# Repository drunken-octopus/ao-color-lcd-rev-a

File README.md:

# ao-color-lcd-rev-a
Revision A of the AlephObjects Color LCD Board, as originally archived from AlephObject's git repos in 2019.

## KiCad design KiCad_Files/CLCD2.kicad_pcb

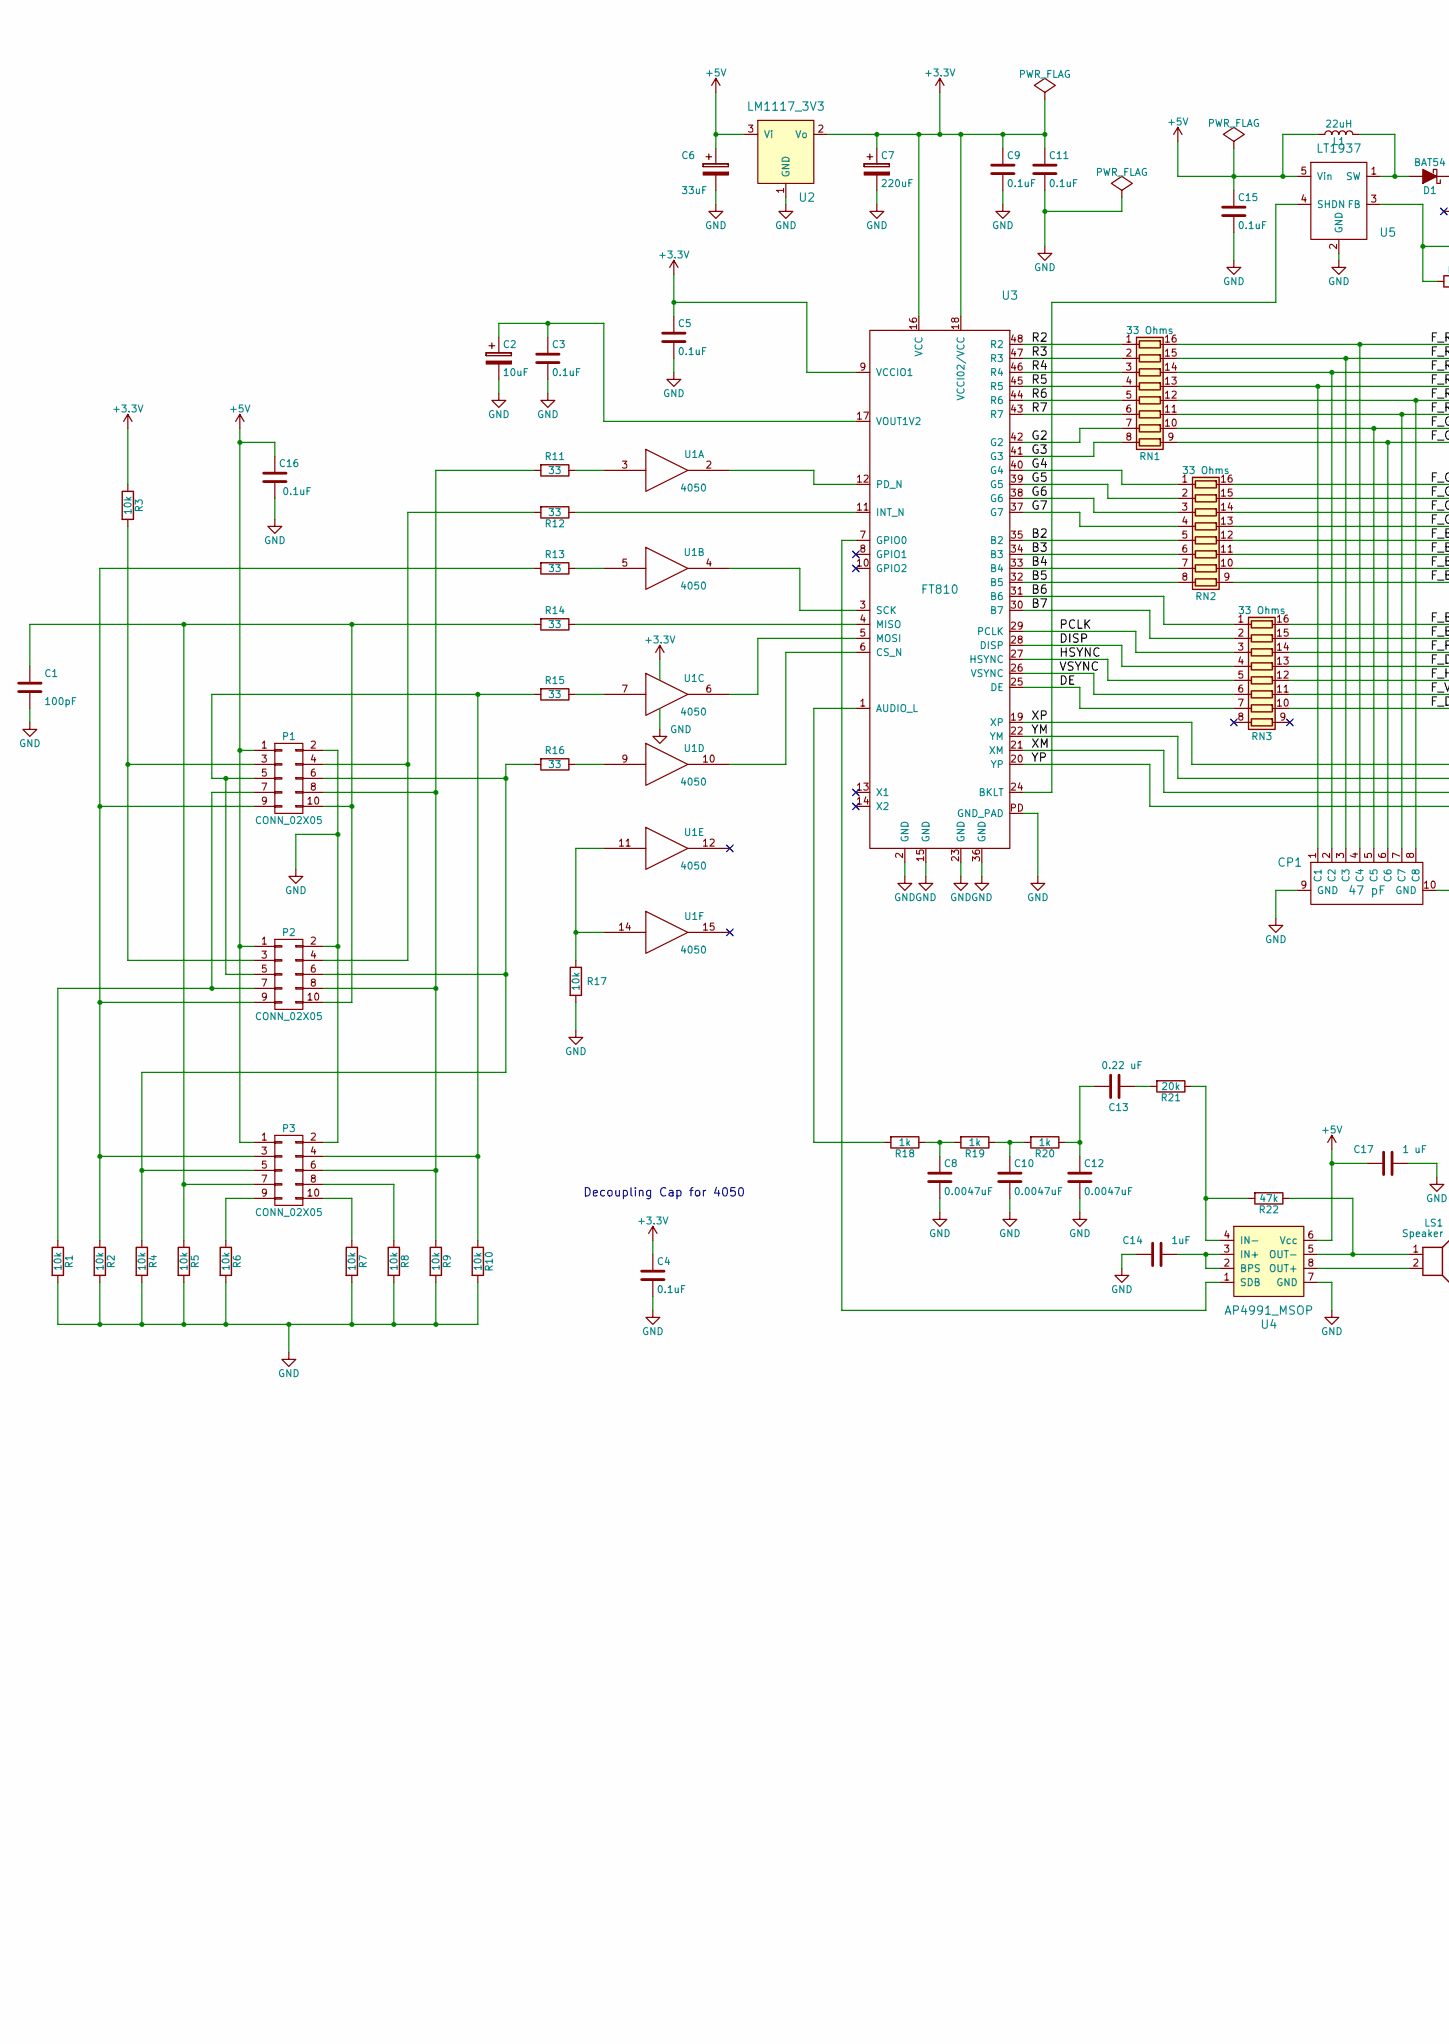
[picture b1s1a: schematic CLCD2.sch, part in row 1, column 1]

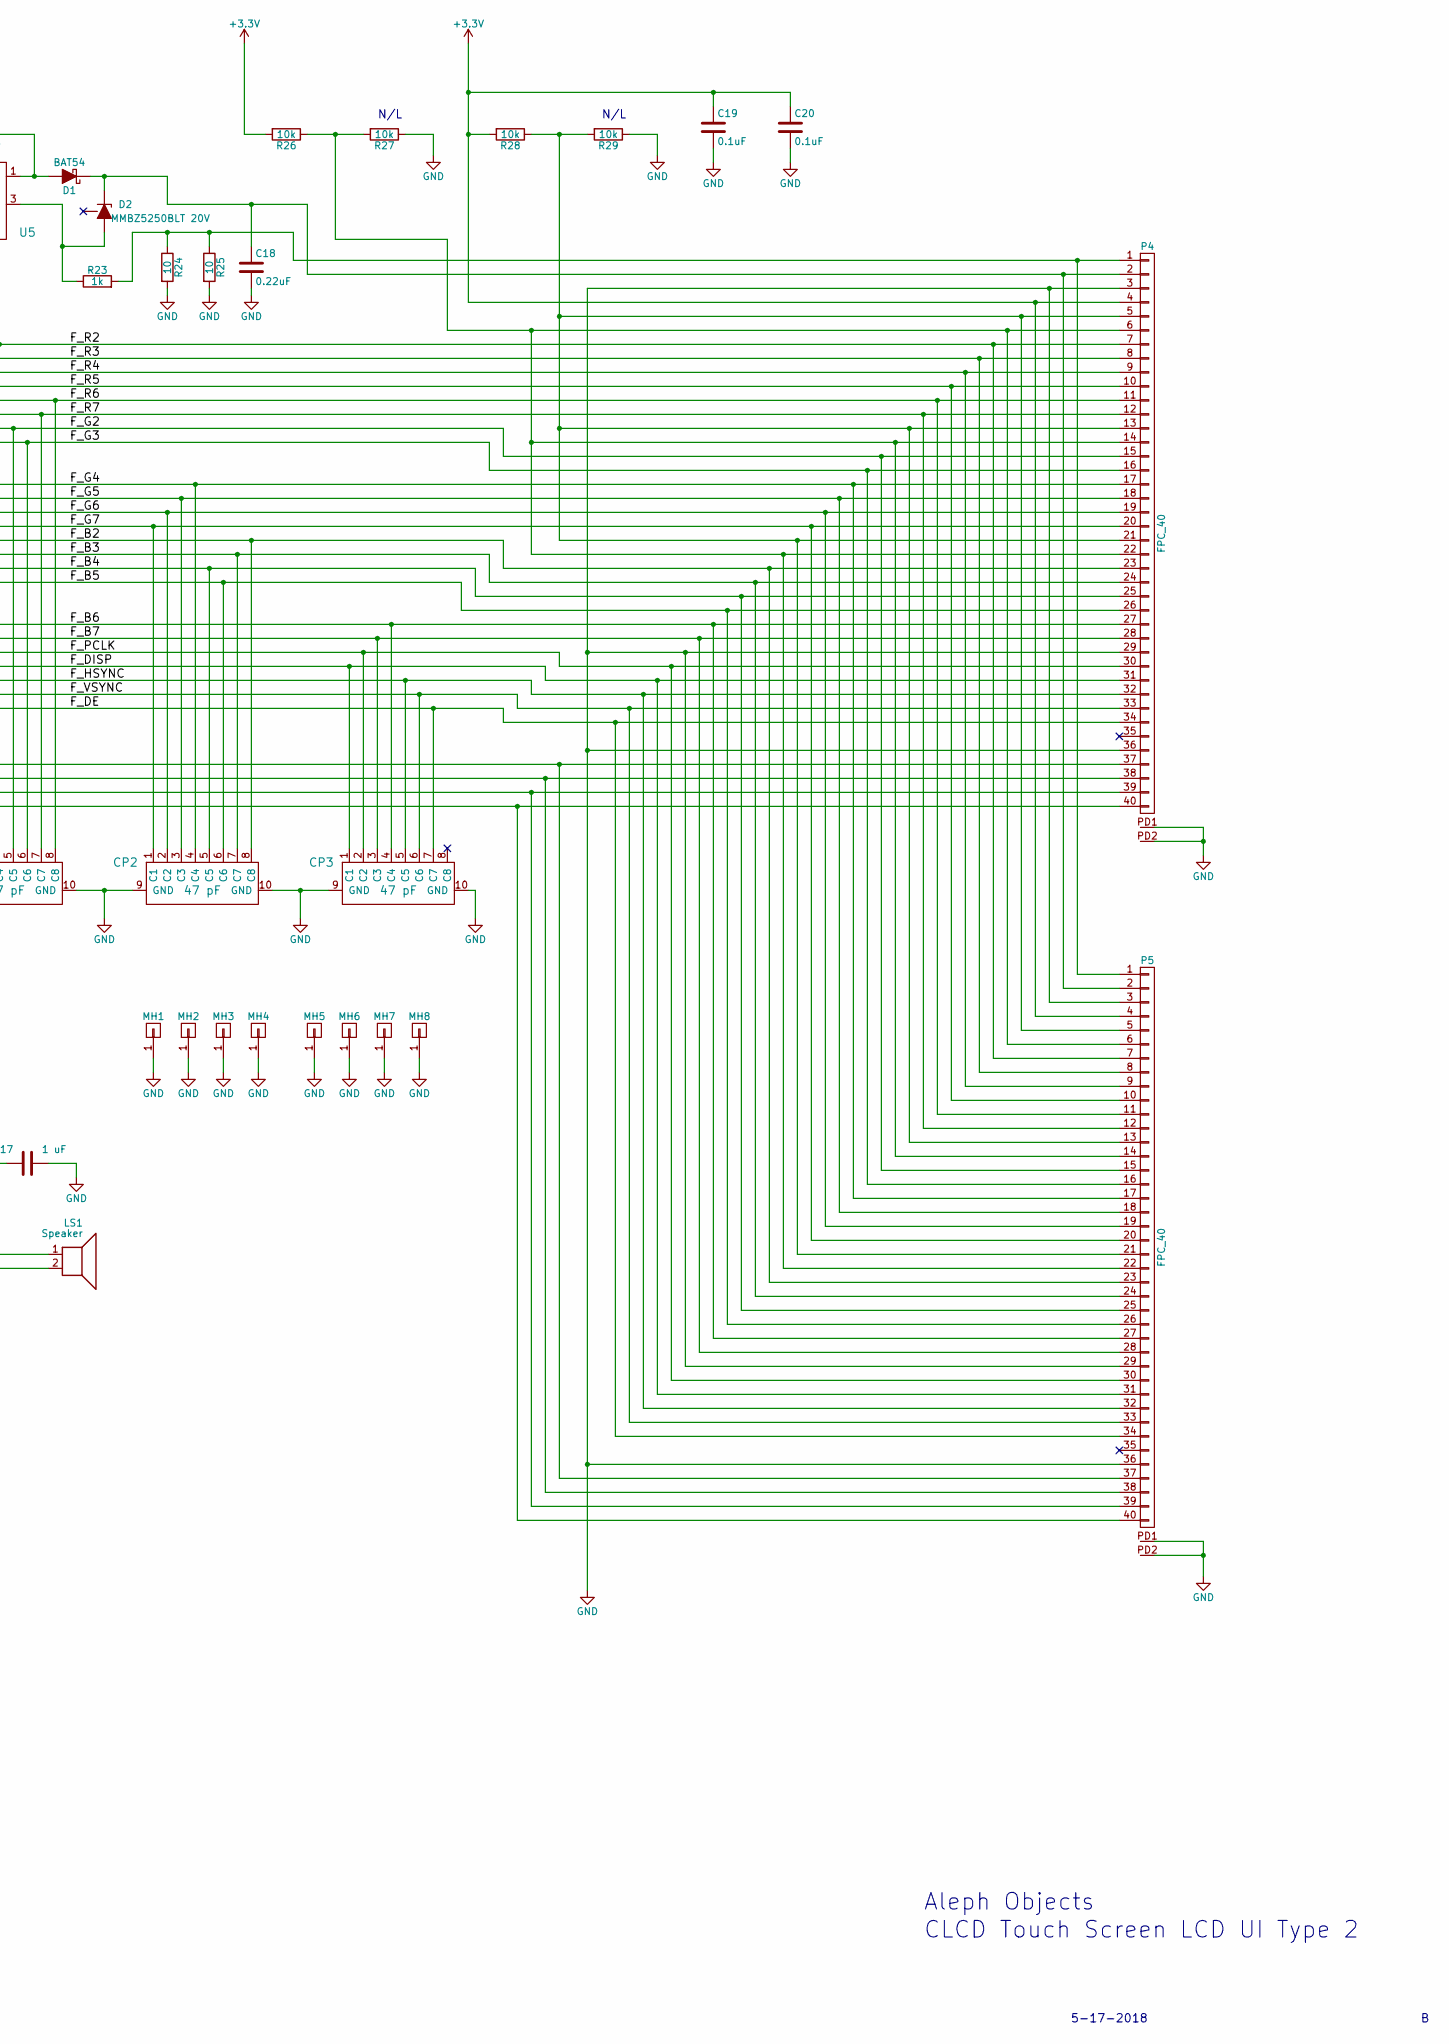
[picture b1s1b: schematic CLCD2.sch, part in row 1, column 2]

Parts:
C1: 100pF; C_0603_HandSoldering
C2: 10uF; TantalC_SizeD_EIA-7343_HandSoldering
C3, C4, C5, C9, C11, C15, C16, C19, C20: 0.1uF; C_0603_HandSoldering
C6: 33uF; TantalC_SizeD_EIA-7343_HandSoldering
C7: 220uF; TantalC_SizeD_EIA-7343_HandSoldering
C8, C10, C12: 0.0047uF; C_0603_HandSoldering
C13: 0.22 uF; C_0603_HandSoldering
C14: 1uF; C_0603_HandSoldering
C17: 1 uF; C_0603_HandSoldering
C18: 0.22uF; C_0603_HandSoldering
CP1, CP2, CP3: 47 pF; CPAK8
D1: BAT54; SOD-123
D2: MMBZ5250BLT 20V; SOT-23
L1: 22uH; Inductor_Taiyo-Yuden_MD-3030
LS1: Speaker; CVS_1508
MH1, MH2, MH3, MH4, MH5, MH6, MH7, MH8: CONN_01X01; MH_M3x6mm
P1, P2, P3: CONN_02X05; IDC_Header_Straight_10pins
P4, P5: FPC_40
R1, R2, R3, R4, R5, R6, R7, R8, R9, R10, R17, R26, R27, R28, R29: 10k; R_0603_HandSoldering
R11, R12, R13, R14, R15, R16: 33; R_0603_HandSoldering
R18, R19, R20, R23: 1k; R_0603_HandSoldering
R21: 20k; R_0603_HandSoldering
R22: 47k; R_0603_HandSoldering
R24, R25: 10; R_0603_HandSoldering
RN1, RN2, RN3: 33 Ohms; RPAK8
U1: 4050; SO-16-N
U2: LM1117_3V3; TO-252-2Lead
U3: FT810; VQFN_48_7x7
U4: AP4991_MSOP; MSOP8
U5: LT1937; SOT-23-5

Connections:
+3V3: C4.1, C5.1, C7.1, C9.1, C11.1, C19.1, C20.1, P4.4, P5.4, R3.1, R26.2, R28.2, U1.1 (VCC), U2.2 (Vo), U3.9 (VCCIO1), U3.16 (VCC), U3.18 (VCCI02/VCC)
+5V: C6.1, C15.1, C16.1, C17.2, L1.1, P1.1, P2.1, P3.1, U2.3 (Vi), U4.6 (Vcc), U5.5 (Vin)
/B2: RN2.5 (R5.1), U3.35 (B2)
/B3: RN2.6 (R6.1), U3.34 (B3)
/B4: RN2.7 (R7.1), U3.33 (B4)
/B5: RN2.8 (R8.1), U3.32 (B5)
/B6: RN3.1 (R1.1), U3.31 (B6)
/B7: RN3.2 (R2.1), U3.30 (B7)
/DE: RN3.7 (R7.1), U3.25 (DE)
/DISP: RN3.4 (R4.1), U3.28 (DISP)
/F_B2: CP2.8 (C8), P4.23, P5.23, RN2.12 (R5.2)
/F_B3: CP2.7 (C7), P4.24, P5.24, RN2.11 (R6.2)
/F_B4: CP2.5 (C5), P4.25, P5.25, RN2.10 (R7.2)
/F_B5: CP2.6 (C6), P4.26, P5.26, RN2.9 (R8.2)
/F_B6: CP3.4 (C4), P4.27, P5.27, RN3.16 (R1.2)
/F_B7: CP3.3 (C3), P4.28, P5.28, RN3.15 (R2.2)
/F_DE: CP3.7 (C7), P4.34, P5.34, RN3.10 (R7.2)
/F_DISP: CP3.1 (C1), P4.31, P5.31, RN3.13 (R4.2)
/F_G2: CP1.5 (C5), P4.15, P5.15, RN1.10 (R7.2)
/F_G3: CP1.6 (C6), P4.16, P5.16, RN1.9 (R8.2)
/F_G4: CP2.4 (C4), P4.17, P5.17, RN2.16 (R1.2)
/F_G5: CP2.3 (C3), P4.18, P5.18, RN2.15 (R2.2)
/F_G6: CP2.2 (C2), P4.19, P5.19, RN2.14 (R3.2)
/F_G7: CP2.1 (C1), P4.20, P5.20, RN2.13 (R4.2)
/F_HSYNC: CP3.5 (C5), P4.32, P5.32, RN3.12 (R5.2)
/F_PCLK: CP3.2 (C2), P4.30, P5.30, RN3.14 (R3.2)
/F_R2: CP1.4 (C4), P4.7, P5.7, RN1.16 (R1.2)
/F_R3: CP1.3 (C3), P4.8, P5.8, RN1.15 (R2.2)
/F_R4: CP1.2 (C2), P4.9, P5.9, RN1.14 (R3.2)
/F_R5: CP1.1 (C1), P4.10, P5.10, RN1.13 (R4.2)
/F_R6: CP1.8 (C8), P4.11, P5.11, RN1.12 (R5.2)
/F_R7: CP1.7 (C7), P4.12, P5.12, RN1.11 (R6.2)
/F_VSYNC: CP3.6 (C6), P4.33, P5.33, RN3.11 (R6.2)
/G2: RN1.7 (R7.1), U3.42 (G2)
/G3: RN1.8 (R8.1), U3.41 (G3)
/G4: RN2.1 (R1.1), U3.40 (G4)
/G5: RN2.2 (R2.1), U3.39 (G5)
/G6: RN2.3 (R3.1), U3.38 (G6)
/G7: RN2.4 (R4.1), U3.37 (G7)
/HSYNC: RN3.5 (R5.1), U3.27 (HSYNC)
/PCLK: RN3.3 (R3.1), U3.29 (PCLK)
/R2: RN1.1 (R1.1), U3.48 (R2)
/R3: RN1.2 (R2.1), U3.47 (R3)
/R4: RN1.3 (R3.1), U3.46 (R4)
/R5: RN1.4 (R4.1), U3.45 (R5)
/R6: RN1.5 (R5.1), U3.44 (R6)
/R7: RN1.6 (R6.1), U3.43 (R7)
/VSYNC: RN3.6 (R6.1), U3.26 (VSYNC)
/XM: P4.39, P5.39, U3.21 (XM)
/XP: P4.37, P5.37, U3.19 (XP)
/YM: P4.38, P5.38, U3.22 (YM)
/YP: P4.40, P5.40, U3.20 (YP)
GND: C1.2, C2.2, C3.2, C4.2, C5.2, C6.2, C7.2, C8.2, C9.2, C10.2, C11.2, C12.2, C14.2, C15.2, C16.2, C17.1, C18.2, C19.2, C20.2, CP1.9 (GND), CP1.10 (GND), CP2.9 (GND), CP2.10 (GND), CP3.9 (GND), CP3.10 (GND), MH1.1, MH2.1, MH3.1, MH4.1, MH5.1, MH6.1, MH7.1, MH8.1, P1.2, P2.2, P3.2, P4.3, P4.29, P4.36, P4.PD1 (PAD), P4.PD2 (PD), P5.3, P5.29, P5.36, P5.PD1 (PAD), P5.PD2 (PD), R1.2, R2.2, R4.2, R5.2, R6.2, R7.2, R8.2, R9.2, R10.2, R17.2, R24.2, R25.2, R27.1, R29.1, U1.8 (VSS), U2.1 (GND), U3.2 (GND), U3.15 (GND), U3.23 (GND), U3.36 (GND), U3.PD (GND_PAD), U4.7 (GND), U5.2 (GND)
unnamed: C1.1, P1.10, P2.10, P3.7, R5.1, R14.2
unnamed: C2.1, C3.1, U3.17 (VOUT1V2)
unnamed: C8.1, R18.1, R19.2
unnamed: C10.1, R19.1, R20.2
unnamed: C12.1, C13.2, R20.1
unnamed: C13.1, R21.2
unnamed: C14.1, U4.2 (BPS), U4.3 (IN+)
unnamed: C18.1, D1.1 (K), D2.3 (K), P4.2, P5.2
unnamed: D1.2 (A), L1.2, U5.1 (SW)
unnamed: D2.1 (A), R23.1, U5.3 (FB)
unnamed: LS1.1, R22.1, U4.5 (OUT-)
unnamed: LS1.2, U4.8 (OUT+)
unnamed: P1.3, P2.3, R3.2
unnamed: P1.4, P2.4, R12.2
unnamed: P1.5, P2.5, P3.4, R10.1, R15.2
unnamed: P1.6, P2.6, P3.5, R4.1, R16.2
unnamed: P1.7, P2.7, R1.1
unnamed: P1.8, P2.8, P3.6, R9.1, R11.2
unnamed: P1.9, P2.9, P3.3, R2.1, R13.2
unnamed: P3.8, R8.1
unnamed: P3.9, R6.1
unnamed: P3.10, R7.1
unnamed: P4.1, P5.1, R23.2, R24.1, R25.1
unnamed: P4.5, P4.13, P4.21, P5.5, P5.13, P5.21, R28.1, R29.2
unnamed: P4.6, P4.14, P4.22, P5.6, P5.14, P5.22, R26.1, R27.2
unnamed: R11.1, U1.3
unnamed: R12.1, U3.11 (INT_N)
unnamed: R13.1, U1.5
unnamed: R14.1, U3.4 (MISO)
unnamed: R15.1, U1.7
unnamed: R16.1, U1.9
unnamed: R17.1, U1.11, U1.14
unnamed: R18.2, U3.1 (AUDIO_L)
unnamed: R21.1, R22.2, U4.4 (IN-)
unnamed: U1.2, U3.12 (PD_N)
unnamed: U1.4, U3.3 (SCK)
unnamed: U1.6, U3.5 (MOSI)
unnamed: U1.10, U3.6 (CS_N)
unnamed: U3.7 (GPIO0), U4.1 (SDB)
unnamed: U3.24 (BKLT), U5.4 (SHDN)

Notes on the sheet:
CLCD Touch Screen LCD UI Type 2
Aleph Objects
5-17-2018
Decoupling Cap for 4050
N/L

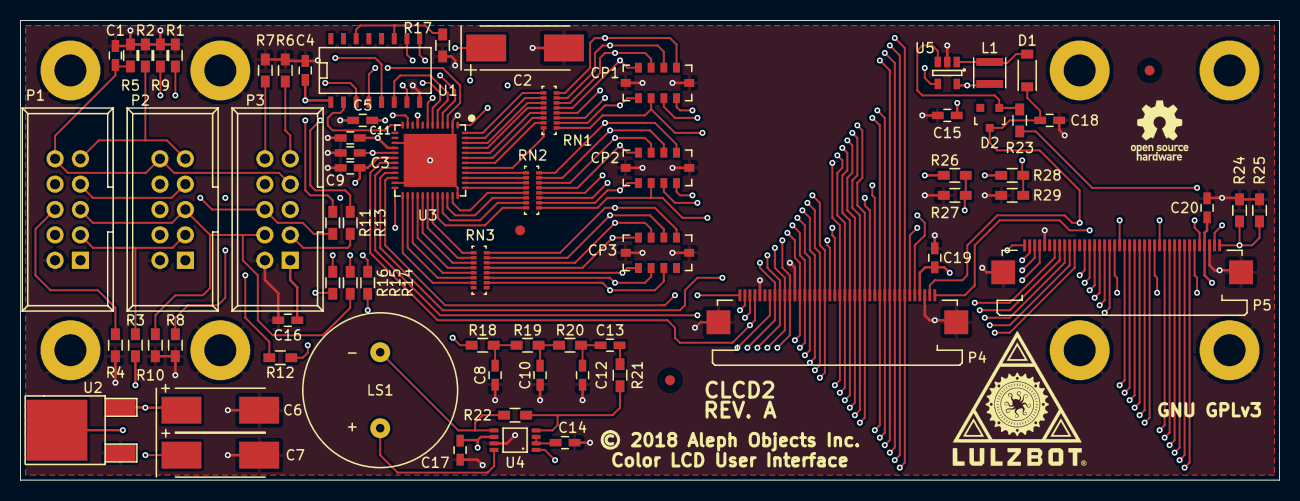
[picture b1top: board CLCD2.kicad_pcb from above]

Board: 4 copper layers, 126.0 x 46.0 mm, 77 parts (0 on the bottom side), 93 nets.

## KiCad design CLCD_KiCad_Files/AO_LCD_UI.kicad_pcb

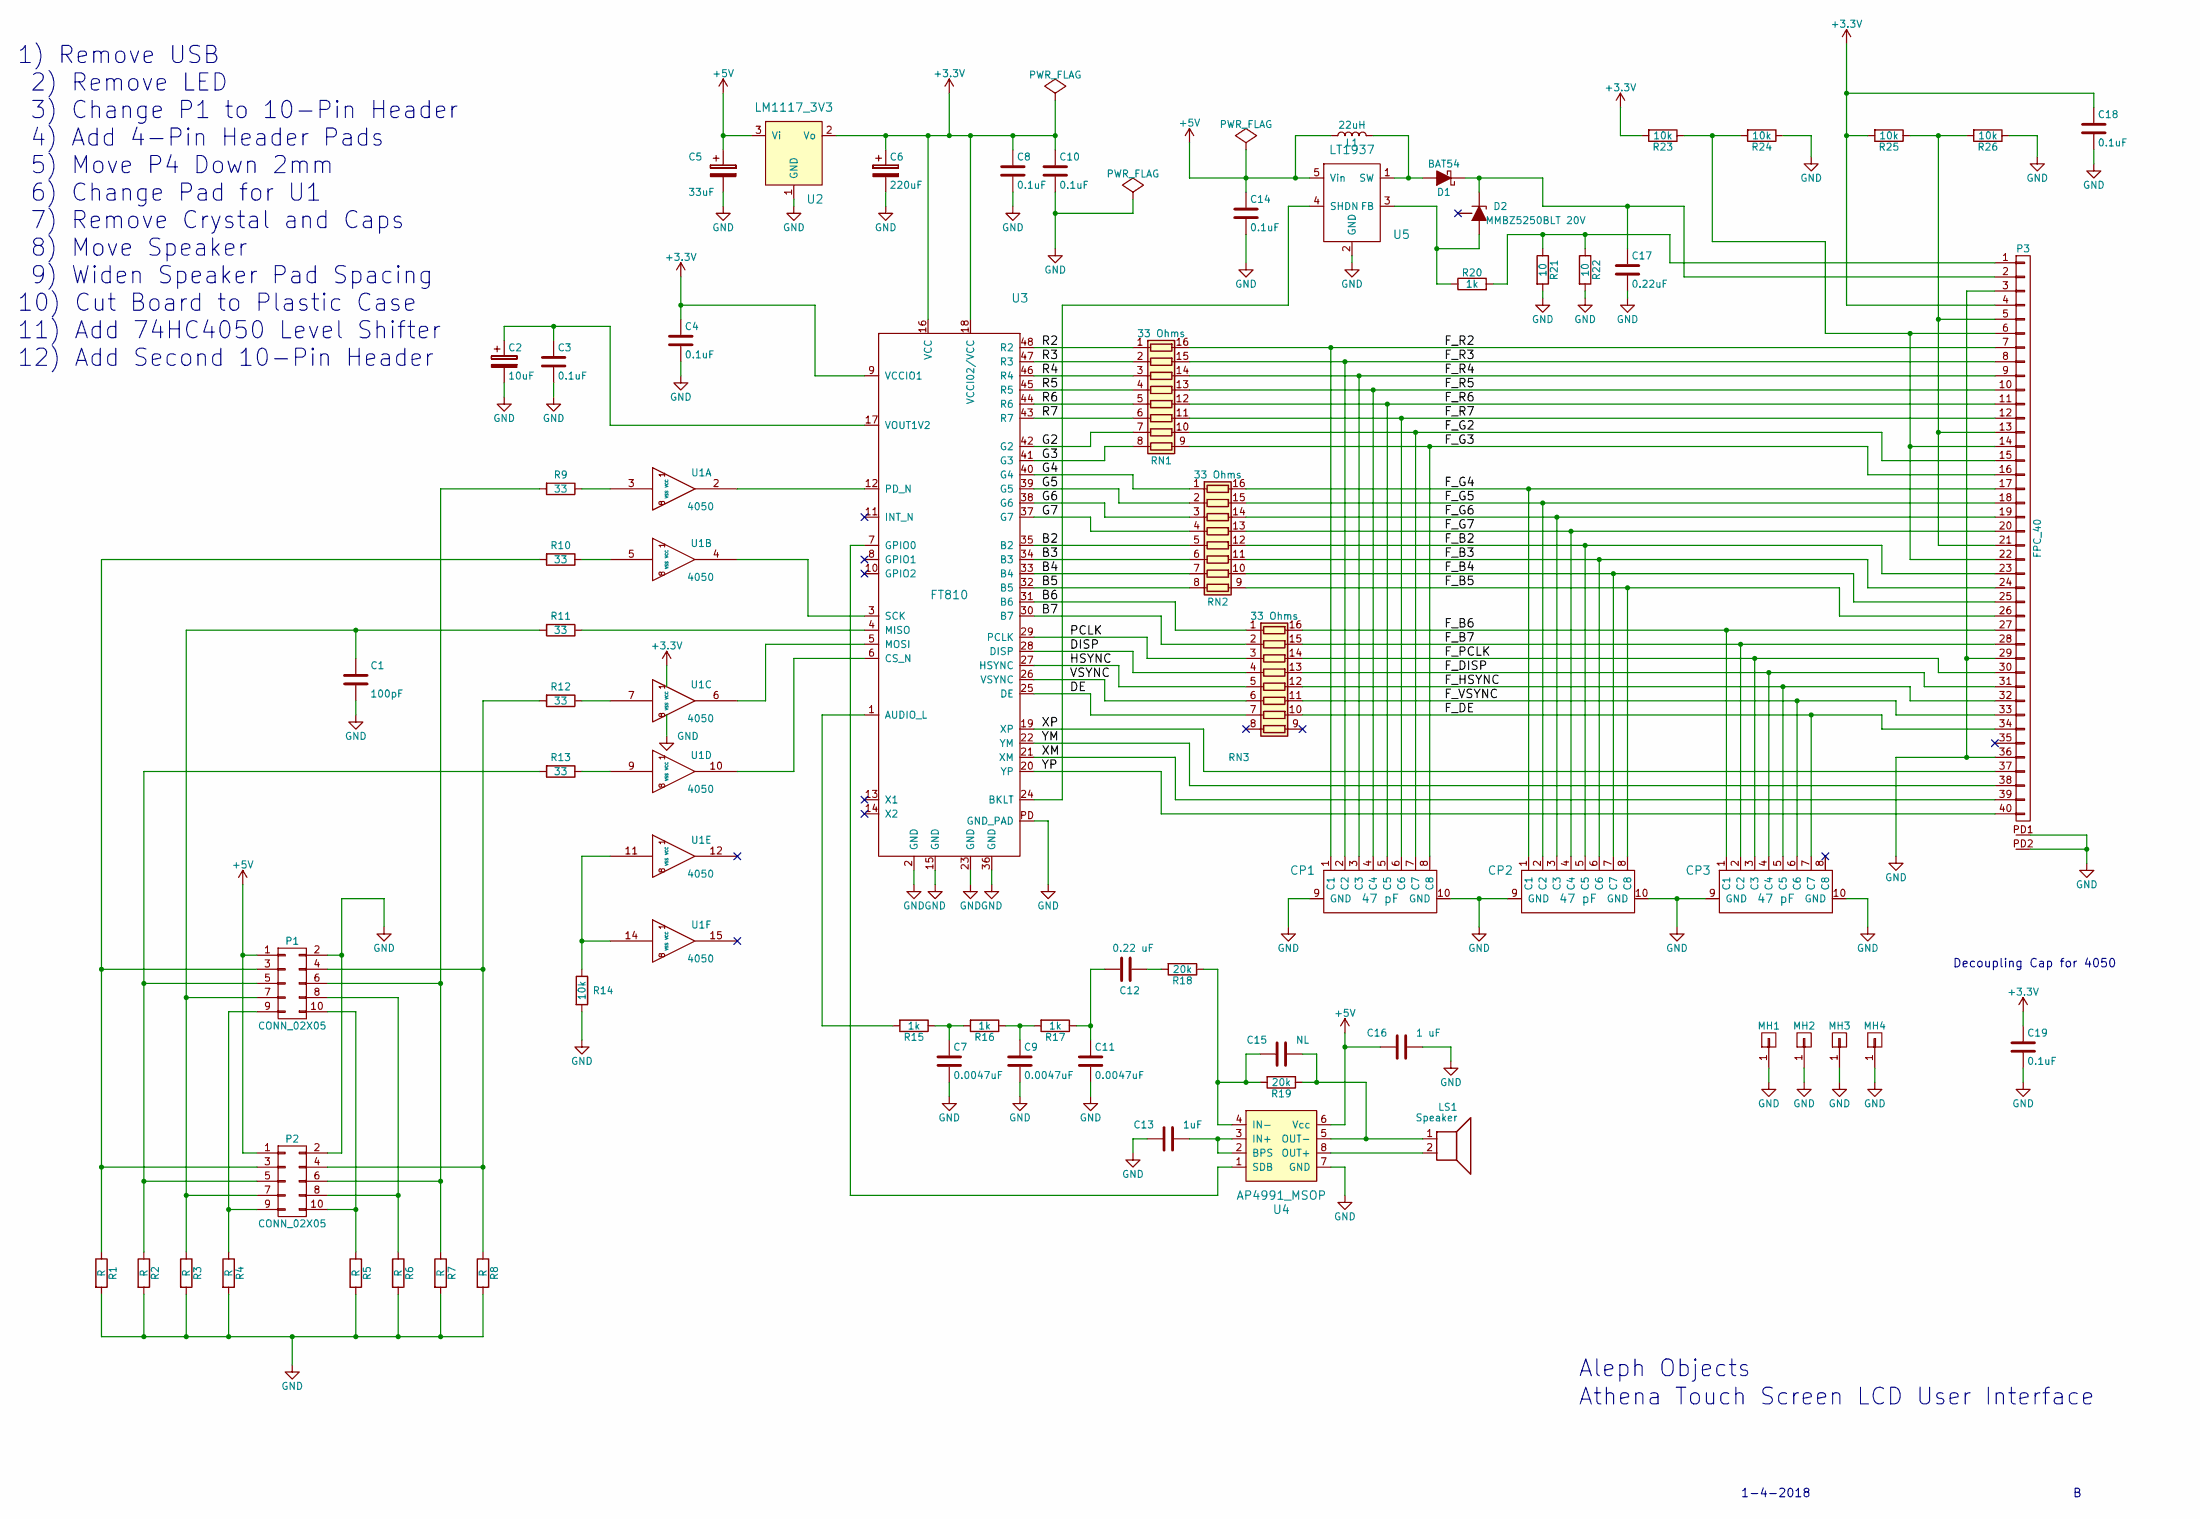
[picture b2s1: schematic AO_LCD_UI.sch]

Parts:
C1: 100pF; C_0603_HandSoldering
C2: 10uF; TantalC_SizeD_EIA-7343_HandSoldering
C3, C4, C8, C10, C14, C18, C19: 0.1uF; C_0603_HandSoldering
C5: 33uF; TantalC_SizeD_EIA-7343_HandSoldering
C6: 220uF; TantalC_SizeD_EIA-7343_HandSoldering
C7, C9, C11: 0.0047uF; C_0603_HandSoldering
C12: 0.22 uF; C_0603_HandSoldering
C13: 1uF; C_0603_HandSoldering
C15: NL; C_0603_HandSoldering
C16: 1 uF; C_0603_HandSoldering
C17: 0.22uF; C_0603_HandSoldering
CP1, CP2, CP3: 47 pF; CPAK8
D1: BAT54; SOD-123
D2: MMBZ5250BLT 20V; SOT-23
L1: 22uH; Inductor_Taiyo-Yuden_MD-3030
LS1: Speaker; CVS_1508
MH1, MH2, MH3, MH4: CONN_01X01; MH_M3x6mm
P1, P2: CONN_02X05; IDC_Header_Straight_10pins
P3: FPC_40
R1, R2, R3, R4, R5, R6, R7, R8: R; R_0603_HandSoldering
R9, R10, R11, R12, R13: 33; R_0603_HandSoldering
R14, R23, R24, R25, R26: 10k; R_0603_HandSoldering
R15, R16, R17, R20: 1k; R_0603_HandSoldering
R18, R19: 20k; R_0603_HandSoldering
R21, R22: 10; R_0603_HandSoldering
RN1, RN2, RN3: 33 Ohms; RPAK8
U1: 4050; SO-16-N
U2: LM1117_3V3; TO-252-2Lead
U3: FT810; VQFN_48_7x7
U4: AP4991_MSOP; MSOP8
U5: LT1937; SOT-23-5

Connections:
+3V3: C4.1, C6.1, C8.1, C10.1, C18.1, C19.1, P3.4, R23.2, R25.2, U1.1 (VCC), U2.2 (Vo), U3.9 (VCCIO1), U3.16 (VCC), U3.18 (VCCI02/VCC)
+5V: C5.1, C14.1, C16.2, L1.1, P1.1, P2.1, U2.3 (Vi), U4.6 (Vcc), U5.5 (Vin)
/B2: RN2.5 (R5.1), U3.35 (B2)
/B3: RN2.6 (R6.1), U3.34 (B3)
/B4: RN2.7 (R7.1), U3.33 (B4)
/B5: RN2.8 (R8.1), U3.32 (B5)
/B6: RN3.1 (R1.1), U3.31 (B6)
/B7: RN3.2 (R2.1), U3.30 (B7)
/DE: RN3.7 (R7.1), U3.25 (DE)
/DISP: RN3.4 (R4.1), U3.28 (DISP)
/F_B2: CP2.5 (C5), P3.23, RN2.12 (R5.2)
/F_B3: CP2.6 (C6), P3.24, RN2.11 (R6.2)
/F_B4: CP2.7 (C7), P3.25, RN2.10 (R7.2)
/F_B5: CP2.8 (C8), P3.26, RN2.9 (R8.2)
/F_B6: CP3.1 (C1), P3.27, RN3.16 (R1.2)
/F_B7: CP3.2 (C2), P3.28, RN3.15 (R2.2)
/F_DE: CP3.7 (C7), P3.34, RN3.10 (R7.2)
/F_DISP: CP3.4 (C4), P3.31, RN3.13 (R4.2)
/F_G2: CP1.7 (C7), P3.15, RN1.10 (R7.2)
/F_G3: CP1.8 (C8), P3.16, RN1.9 (R8.2)
/F_G4: CP2.1 (C1), P3.17, RN2.16 (R1.2)
/F_G5: CP2.2 (C2), P3.18, RN2.15 (R2.2)
/F_G6: CP2.3 (C3), P3.19, RN2.14 (R3.2)
/F_G7: CP2.4 (C4), P3.20, RN2.13 (R4.2)
/F_HSYNC: CP3.5 (C5), P3.32, RN3.12 (R5.2)
/F_PCLK: CP3.3 (C3), P3.30, RN3.14 (R3.2)
/F_R2: CP1.1 (C1), P3.7, RN1.16 (R1.2)
/F_R3: CP1.2 (C2), P3.8, RN1.15 (R2.2)
/F_R4: CP1.3 (C3), P3.9, RN1.14 (R3.2)
/F_R5: CP1.4 (C4), P3.10, RN1.13 (R4.2)
/F_R6: CP1.5 (C5), P3.11, RN1.12 (R5.2)
/F_R7: CP1.6 (C6), P3.12, RN1.11 (R6.2)
/F_VSYNC: CP3.6 (C6), P3.33, RN3.11 (R6.2)
/G2: RN1.7 (R7.1), U3.42 (G2)
/G3: RN1.8 (R8.1), U3.41 (G3)
/G4: RN2.1 (R1.1), U3.40 (G4)
/G5: RN2.2 (R2.1), U3.39 (G5)
/G6: RN2.3 (R3.1), U3.38 (G6)
/G7: RN2.4 (R4.1), U3.37 (G7)
/HSYNC: RN3.5 (R5.1), U3.27 (HSYNC)
/PCLK: RN3.3 (R3.1), U3.29 (PCLK)
/R2: RN1.1 (R1.1), U3.48 (R2)
/R3: RN1.2 (R2.1), U3.47 (R3)
/R4: RN1.3 (R3.1), U3.46 (R4)
/R5: RN1.4 (R4.1), U3.45 (R5)
/R6: RN1.5 (R5.1), U3.44 (R6)
/R7: RN1.6 (R6.1), U3.43 (R7)
/VSYNC: RN3.6 (R6.1), U3.26 (VSYNC)
/XM: P3.39, U3.21 (XM)
/XP: P3.37, U3.19 (XP)
/YM: P3.38, U3.22 (YM)
/YP: P3.40, U3.20 (YP)
GND: C1.2, C2.2, C3.2, C4.2, C5.2, C6.2, C7.2, C8.2, C9.2, C10.2, C11.2, C13.2, C14.2, C16.1, C17.2, C18.2, C19.2, CP1.9 (GND), CP1.10 (GND), CP2.9 (GND), CP2.10 (GND), CP3.9 (GND), CP3.10 (GND), MH1.1, MH2.1, MH3.1, MH4.1, P1.2, P2.2, P3.3, P3.29, P3.36, P3.PD1 (PAD), P3.PD2 (PD), R1.2, R2.2, R3.2, R4.2, R5.2, R6.2, R7.2, R8.2, R14.2, R21.2, R22.2, R24.1, R26.1, U1.8 (VSS), U2.1 (GND), U3.2 (GND), U3.15 (GND), U3.23 (GND), U3.36 (GND), U3.PD (GND_PAD), U4.7 (GND), U5.2 (GND)
unnamed: C1.1, P1.7, P2.7, R3.1, R11.2
unnamed: C2.1, C3.1, U3.17 (VOUT1V2)
unnamed: C7.1, R15.1, R16.2
unnamed: C9.1, R16.1, R17.2
unnamed: C11.1, C12.2, R17.1
unnamed: C12.1, R18.2
unnamed: C13.1, U4.2 (BPS), U4.3 (IN+)
unnamed: C15.1, LS1.1, R19.1, U4.5 (OUT-)
unnamed: C15.2, R18.1, R19.2, U4.4 (IN-)
unnamed: C17.1, D1.1 (K), D2.3 (K), P3.2
unnamed: D1.2 (A), L1.2, U5.1 (SW)
unnamed: D2.1 (A), R20.1, U5.3 (FB)
unnamed: LS1.2, U4.8 (OUT+)
unnamed: P1.3, P2.3, R1.1, R10.2
unnamed: P1.4, P2.4, R8.1, R12.2
unnamed: P1.5, P2.5, R2.1, R13.2
unnamed: P1.6, P2.6, R7.1, R9.2
unnamed: P1.8, P2.8, R6.1
unnamed: P1.9, P2.9, R4.1
unnamed: P1.10, P2.10, R5.1
unnamed: P3.1, R20.2, R21.1, R22.1
unnamed: P3.5, P3.13, P3.21, R25.1, R26.2
unnamed: P3.6, P3.14, P3.22, R23.1, R24.2
unnamed: R9.1, U1.3
unnamed: R10.1, U1.5
unnamed: R11.1, U3.4 (MISO)
unnamed: R12.1, U1.7
unnamed: R13.1, U1.9
unnamed: R14.1, U1.11, U1.14
unnamed: R15.2, U3.1 (AUDIO_L)
unnamed: U1.2, U3.12 (PD_N)
unnamed: U1.4, U3.3 (SCK)
unnamed: U1.6, U3.5 (MOSI)
unnamed: U1.10, U3.6 (CS_N)
unnamed: U3.7 (GPIO0), U4.1 (SDB)
unnamed: U3.24 (BKLT), U5.4 (SHDN)

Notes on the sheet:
Athena Touch Screen LCD User Interface
Aleph Objects
1-4-2018
1) Remove USB 2) Remove LED 3) Change P1 to 10-Pin Header 4) Add 4-Pin Header Pads 5) Move P4 Down 2mm 6) Change Pad for U1 7) Remove Crystal and Caps 8) Move Speaker 9) Widen Speaker Pad Spacing 10) Cut Board to Plastic Case 11) Add 74HC4050 Level Shifter 12) Add Second 10-Pin Header
Decoupling Cap for 4050

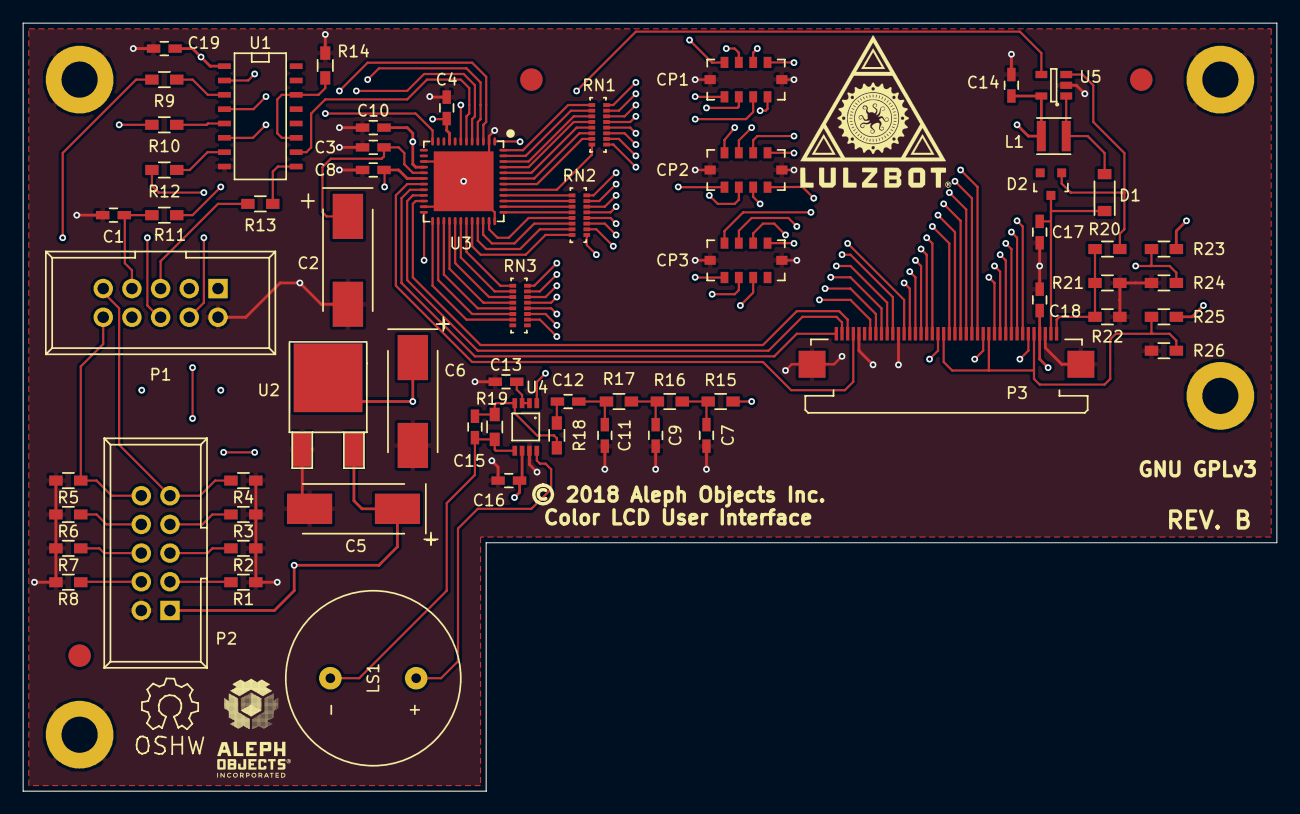
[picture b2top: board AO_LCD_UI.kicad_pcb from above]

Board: 4 copper layers, 111.0 x 68.0 mm, 67 parts (0 on the bottom side), 89 nets.

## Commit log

2017-07-03 Initial files for Color LCD Touch Controller.
2017-09-26 Color LCD Module schematics and board files.
2018-02-08 Added files of REV B Color LCD Board (CLCD) Gerbers and KiCad files.
2018-02-08 Added latest AO_Color_LCD C Files as of 2-8-18.
2018-02-20 Added License files to repo.
2018-04-19 Update License from APGL to GPL
2018-08-24 Remove duplicate aotctl directory
2018-08-24 Remove old test firmware
2018-08-24 Remove old KiCad file
2018-08-24 Remove old firmware
2018-08-24 Update KiCad source files to latest design
2018-08-24 Remove previous rev gerber files
2018-08-24 Remove old rev KiCad files
2018-08-24 Update gerber files
2023-07-22 Added PDF version of schematics

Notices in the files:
CLCD_KiCad_Files/AO_LCD_UI.kicad_pcb:
GNU GPLv3
© 2018 Aleph Objects Inc.
